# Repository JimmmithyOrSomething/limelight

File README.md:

Glasses with built in EEG and EMG

I built this because I've always been so interested by our brains, our whole world and everything we know is a constuction of how they process senses and even in this small way I want to learn more about how they work.

| item | price | amount | link | info | total |
| ------- | --- | --- |--- | --- | --- |
| Esp-32 | N/A | 1 | [here](https://www.adafruit.com/product/5400) |The brains of the system| 87.19|
| PCB| N/A | 5 | [here](https://jlcpcb.com/) |Amp and wiring|
|glasses	| free	| 1| 	N/A |	3d printable amp holder|
| flux pen| 2.44 | 1 | [here](https://www.aliexpress.us/item/3256808243822446.html?spm=a2g0o.productlist.main.1.49ae48cbyMQqs5&algo_pvid=35e7510d-5270-4345-b864-686b3629ecf1&algo_exp_id=35e7510d-5270-4345-b864-686b3629ecf1-0&pdp_ext_f=%7B%22order%22%3A%221792%22%2C%22spu_best_type%22%3A%22price%22%2C%22eval%22%3A%221%22%2C%22orig_sl_item_id%22%3A%221005008430137198%22%2C%22orig_item_id%22%3A%221005007346959832%22%7D&pdp_npi=6%40dis%21USD%215.31%212.44%21%21%2137.94%2117.45%21%402101ec1a17544436318778323e39b4%2112000045059796687%21sea%21US%210%21ABX%211%210%21&curPageLogUid=9gprCPyANdN1&utparam-url=scene%3Asearch%7Cquery_from%3A) | for soldering|
|micro solder tips| .99| 1 | [here](https://www.aliexpress.us/item/3256805657675571.html?spm=a2g0o.productlist.main.8.4ae47454jRk7uW&aem_p4p_detail=202508051822223214808784592390000925811&algo_pvid=0da8aec6-6387-49a0-b222-89de350f7cd6&algo_exp_id=0da8aec6-6387-49a0-b222-89de350f7cd6-7&pdp_ext_f=%7B%22order%22%3A%22851%22%2C%22eval%22%3A%221%22%7D&pdp_npi=6%40dis%21USD%211.52%210.99%21%21%2110.89%217.12%21%402103273e17544433426261254ee0d0%2112000034549588298%21sea%21US%210%21ABX%211%210%21&curPageLogUid=XD2mQbIyJrUv&utparam-url=scene%3Asearch%7Cquery_from%3A&search_p4p_id=202508051822223214808784592390000925811_6)| for soldering
|Electrodes	|46 |12	|	[here](https://www.aliexpress.us/item/3256803886075504.html?spm=a2g0o.productlist.main.4.59c81e0bOoxuap&aem_p4p_detail=202508051814269813486045065880000922915&algo_pvid=de5d4859-1eeb-4ae7-b5d8-d84f5ccd8ec2&algo_exp_id=de5d4859-1eeb-4ae7-b5d8-d84f5ccd8ec2-3&pdp_ext_f=%7B%22order%22%3A%227%22%2C%22eval%22%3A%221%22%7D&pdp_npi=6%40dis%21USD%2138.75%2138.75%21%21%2138.75%2138.75%21%402101e7f617544428667672676e5f43%2112000027945523742%21sea%21US%210%21ABX%211%210%21&curPageLogUid=VxrAzmOPV8pg&utparam-url=scene%3Asearch%7Cquery_from%3A&search_p4p_id=202508051814269813486045065880000922915_1) |	For reading brainwaves|
|Electrode gel	| 	10 | 1|	[here](https://www.walmart.com/ip/Spectra-360-Electrode-Gel-250gm-8-5oz-Tube-Each/792282565?wmlspartner=wlpa&selectedSellerId=101189557&selectedOfferId=6CC344D59E7B318697062A237A010418&conditionGroupCode=1&adid=22222222222000000000&wmlspartner=wmtlabs&wl0=e&wl1=o&wl2=c&wl3=10352200394&wl4=pla-1103028060075&wl5=103047&wl6=&wl7=&wl10=Walmart&wl11=Online&wl12=792282565_10001208918&wl14=spectra%20360%20electrode%20gel&veh=sem&gclid=5b0bcb0ccfa51ba3db34a37e5ae30c59&gclsrc=3p.ds&msclkid=5b0bcb0ccfa51ba3db34a37e5ae30c59)	| For conductive connection  (I couldn't find one on aliExpress)|
|Caps and resistors |	2.76 | 7|	[here](https://lcsc.com/)	| needed to swich EEG and EMG (if I can't ship with the PCB I will pay for this) |

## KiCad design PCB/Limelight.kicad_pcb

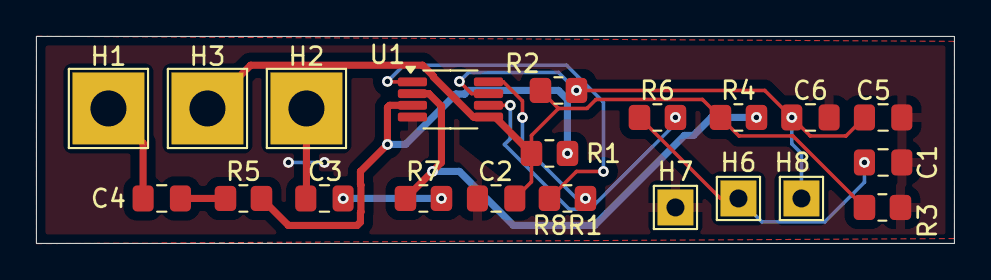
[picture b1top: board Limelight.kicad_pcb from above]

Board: 2 copper layers, 51.0 x 11.5 mm, 21 parts (0 on the bottom side), 13 nets.

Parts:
C1, C3, C4: C_0805_2012Metric_Pad1.18x1.45mm_HandSolder
C2: 1µF; C_0805_2012Metric_Pad1.18x1.45mm_HandSolder
C5: 100 nF; C_0805_2012Metric_Pad1.18x1.45mm_HandSolder
C6: 10 µF; C_0805_2012Metric_Pad1.18x1.45mm_HandSolder
H1, H2, H3: MountingHole_Pad; TestPoint_THTPad_4.0x4.0mm_Drill2.0mm
H6: A0 pad; TestPoint_THTPad_2.0x2.0mm_Drill1.0mm
H7: GND pad; TestPoint_THTPad_2.0x2.0mm_Drill1.0mm
H8: VCC pad 3.3v; TestPoint_THTPad_2.0x2.0mm_Drill1.0mm
R1: 10MR; R_0805_2012Metric_Pad1.20x1.40mm_HandSolder
R2, R3, R6: 10kR; R_0805_2012Metric_Pad1.20x1.40mm_HandSolder
R4, R7, R8R1: R_0805_2012Metric_Pad1.20x1.40mm_HandSolder
R5: 1kR; R_0805_2012Metric_Pad1.20x1.40mm_HandSolder
U1: INA333xxDGK; VSSOP-8_3x3mm_P0.65mm

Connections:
/A0: C1.1, H6.1, R6.1
GND: C1.2, C2.1, C5.2, C6.2, H7.1, R3.1, U1.4 (V-)
unnamed: C3.1, H2.1
unnamed: C3.2, R7.2
unnamed: C4.1, H1.1
unnamed: C4.2, R5.1
unnamed: R6.2, U1.6
unnamed: R8R1.1, U1.1 (Rg)
unnamed: R8R1.2, U1.8 (Rg)
unnamed: R1.2, R5.2, U1.3 (+)
unnamed: R4.2, R7.1, U1.2 (-)
unnamed: C2.2, H3.1, R1.1, R2.1, R3.2, R4.1, U1.5 (Ref)
VCC: C5.1, C6.1, H8.1, R2.2, U1.7 (V+)

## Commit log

2025-07-10 Rename limelightESP.ino to code/limelightESP.ino
2025-07-12 Rename limelight_.f3d to limelight_.f3d
2025-07-12 Rename Limelight.kicad_pro to Limelight.kicad_pro
2025-07-14 Rename Limelight.kicad_pro to PCB/Limelight.kicad_pro
2025-08-06 Rename Limelight.step to PCB/Limelight.step
